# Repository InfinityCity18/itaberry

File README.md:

# Itaberry

Itaberry is a program combining a web interface, and SPI displays controllers, running on a Raspberry Pi 4B. 
It was designed as a way to have animated/changeable pins on an "Itabag".

Frontend uses Svelte, SPI displays are controlled using Rust and Raspberry Pi GPIO. To connect all the displays nicely, a custom PCB was designed.

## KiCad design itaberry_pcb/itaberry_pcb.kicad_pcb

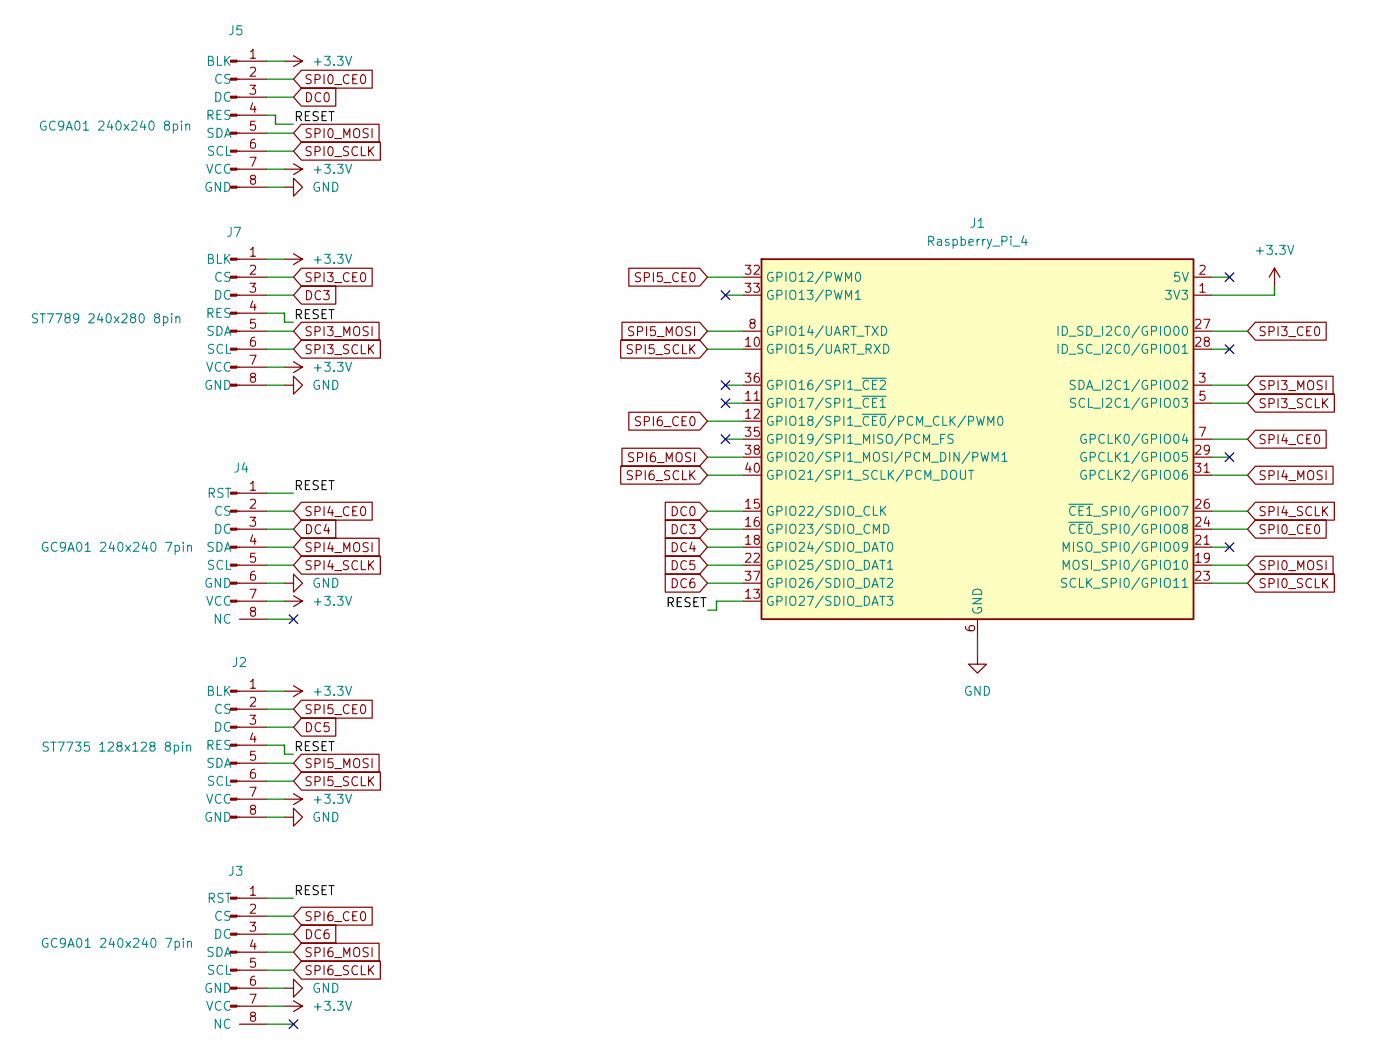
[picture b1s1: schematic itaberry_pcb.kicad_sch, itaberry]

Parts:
J1: Raspberry_Pi_4; PinHeader_2x20_P2.54mm_Vertical_SMD; LCSC Part # C2685175
J2: ST7735 128x128 8pin; PinHeader_1x08_P2.54mm_Vertical_SMD_Pin1Left; LCSC Part # C5160791
J3, J4: GC9A01 240x240 7pin; PinHeader_1x08_P2.54mm_Vertical_SMD_Pin1Left; LCSC Part # C5160791
J5: GC9A01 240x240 8pin; PinHeader_1x08_P2.54mm_Vertical_SMD_Pin1Left; LCSC Part # C5160791
J7: ST7789 240x280 8pin; PinHeader_1x08_P2.54mm_Vertical_SMD_Pin1Left; LCSC Part # C5160791

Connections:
+3.3V: J1.1 (3V3), J1.17 (3V3), J2.1 (BLK), J2.7 (VCC), J3.7 (VCC), J4.7 (VCC), J5.1 (BLK), J5.7 (VCC), J7.1 (BLK), J7.7 (VCC)
/RESET: J1.13 (GPIO27/SDIO_DAT3), J2.4 (RES), J3.1 (RST), J4.1 (RST), J5.4 (RES), J7.4 (RES)
DC0: J1.15 (GPIO22/SDIO_CLK), J5.3 (DC)
DC3: J1.16 (GPIO23/SDIO_CMD), J7.3 (DC)
DC4: J1.18 (GPIO24/SDIO_DAT0), J4.3 (DC)
DC5: J1.22 (GPIO25/SDIO_DAT1), J2.3 (DC)
DC6: J1.37 (GPIO26/SDIO_DAT2), J3.3 (DC)
GND: J1.6 (GND), J1.9 (GND), J1.14 (GND), J1.20 (GND), J1.25 (GND), J1.30 (GND), J1.34 (GND), J1.39 (GND), J2.8 (GND), J3.6 (GND), J4.6 (GND), J5.8 (GND), J7.8 (GND)
SPI0_CE0: J1.24 (~CE0_SPI0/GPIO08), J5.2 (CS)
SPI0_MOSI: J1.19 (MOSI_SPI0/GPIO10), J5.5 (SDA)
SPI0_SCLK: J1.23 (SCLK_SPI0/GPIO11), J5.6 (SCL)
SPI3_CE0: J1.27 (ID_SD_I2C0/GPIO00), J7.2 (CS)
SPI3_MOSI: J1.3 (SDA_I2C1/GPIO02), J7.5 (SDA)
SPI3_SCLK: J1.5 (SCL_I2C1/GPIO03), J7.6 (SCL)
SPI4_CE0: J1.7 (GPCLK0/GPIO04), J4.2 (CS)
SPI4_MOSI: J1.31 (GPCLK2/GPIO06), J4.4 (SDA)
SPI4_SCLK: J1.26 (~CE1_SPI0/GPIO07), J4.5 (SCL)
SPI5_CE0: J1.32 (GPIO12/PWM0), J2.2 (CS)
SPI5_MOSI: J1.8 (GPIO14/UART_TXD), J2.5 (SDA)
SPI5_SCLK: J1.10 (GPIO15/UART_RXD), J2.6 (SCL)
SPI6_CE0: J1.12 (GPIO18/SPI1_~CE0/PCM_CLK/PWM0), J3.2 (CS)
SPI6_MOSI: J1.38 (GPIO20/SPI1_MOSI/PCM_DIN/PWM1), J3.4 (SDA)
SPI6_SCLK: J1.40 (GPIO21/SPI1_SCLK/PCM_DOUT), J3.5 (SCL)

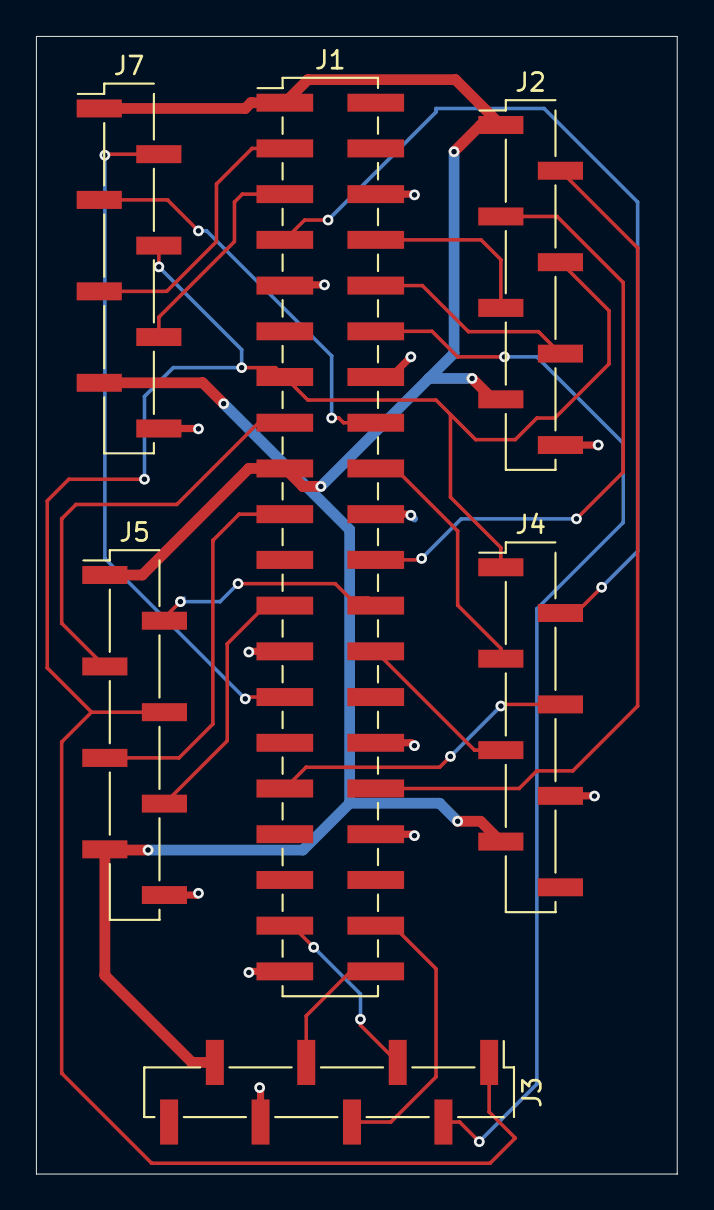
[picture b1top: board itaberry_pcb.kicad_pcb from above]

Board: 2 copper layers, 35.6 x 63.2 mm, 6 parts (0 on the bottom side), 23 nets.

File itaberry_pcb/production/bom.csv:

Designator,Footprint,Quantity,Value,LCSC Part #
J1,PinHeader_2x20_P2.54mm_Vertical_SMD,1,Raspberry_Pi_4,C2685175
J2,PinHeader_1x08_P2.54mm_Vertical_SMD_Pin1Left,1,ST7735 128x128 8pin,C5160791
"J3, J4",PinHeader_1x08_P2.54mm_Vertical_SMD_Pin1Left,2,GC9A01 240x240 7pin,C5160791
J5,PinHeader_1x08_P2.54mm_Vertical_SMD_Pin1Left,1,GC9A01 240x240 8pin,C5160791
J7,PinHeader_1x08_P2.54mm_Vertical_SMD_Pin1Left,1,ST7789 240x280 8pin,C5160791
